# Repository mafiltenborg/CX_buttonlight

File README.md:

# What's this?
Incandescent bulbs are used in the most bizarre places in older cars - and they're often hard to replace when they burn out.
This repo holds an absolutely tiny pcb with LEDs, designed to replace one of these specialty bulb-PITAs - once and for all!

# Which & where
The particular bulb being replicated/upgraded is located inside the toggle-contacts for eg electric windows or demister switch in the Citroen CX S2 (late model '86 onwards). Replacing requires disassembly and fairly good motorskills on your part. The design uses 0805 SMDs, making it, well, possible as least. I'm too old for 0402...

# How
To replace, get hold of a number of the little PCBs (17 x 5,5mm) and solder them up. 
Next, for every contact you want to upgrade, do
* Open up your contact and extract the yellow opaque plastic thingamabob.
* Remove the burnt-out bulb and slide in a LED-replacement circuit. Re-wire the yellow thingamabob.
* Plonk in the thingamabob and do a test run. If it doesn't light up, try turning it 180 degrees - polarity matters...

Further tweaks may include modding the value of R2 to get a sensible light output. LEDs are in fact quite bright and 'much' may not be the right choice for you. The circuit is not designed for power hungry LEDs as it uses a linear regulator. 

LEDs differ. To figure out the value of R2, use the formula

Vout = 1.25 * (1 + R2/R1)

To calculate.

Don't modify R1, as this may create instability.

-----------------------
Nov. 2025 update: This design has sparked development of a more userfriendly successor. More light and less hassle too. If interested, have a look [here](https://github.com/mafiltenborg/CX-buttonlight_v2)...

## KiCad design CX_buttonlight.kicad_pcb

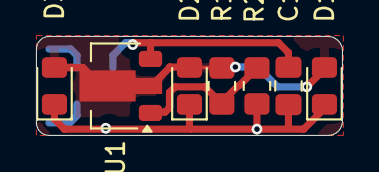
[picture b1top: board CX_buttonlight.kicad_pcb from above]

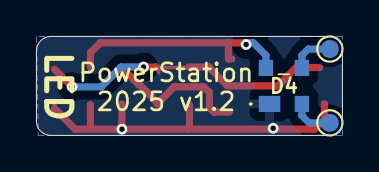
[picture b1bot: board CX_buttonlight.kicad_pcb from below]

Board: 2 copper layers, 17.0 x 5.5 mm, 10 parts (3 on the bottom side), 6 nets.

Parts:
C1: 100nF; C_0805_2012Metric_Pad1.18x1.45mm_HandSolder
D1, D2, D3: LED; LED_0805_2012Metric_Pad1.15x1.40mm_HandSolder
D4: BAS4002ARPPE6327HTSA1
Ground1: Ground; TestPoint_Pad_D1.0mm
R1: 470R; R_0805_2012Metric_Pad1.20x1.40mm_HandSolder
R2: 220R; R_0805_2012Metric_Pad1.20x1.40mm_HandSolder
Supply1: 12V; TestPoint_Pad_D1.0mm
U1: LM317L_SOT-89; SOT-89-3

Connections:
GND: C1.2, D1.1 (K), D2.1 (K), D3.1 (K), D4.1 (-), R2.1
unnamed: D1.2 (A), D2.2 (A), D3.2 (A), R1.2, U1.2 (VO)
unnamed: C1.1, D4.4 (+), U1.3 (VI)
unnamed: D4.2 (~_1), Supply1.1
unnamed: D4.3 (~_2), Ground1.1
unnamed: R1.1, R2.2, U1.1 (ADJ)

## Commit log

2025-10-21 v1.0
2025-10-21 v1.1 - med beskyttelsesdiode
2025-10-21 Modify README with more info.
2025-10-21 Add lockfiles to .gitignore
2025-10-24 updated design (tweaks + specs), sent to JLCPCB
2025-11-12 Update README.md
    Add link to v2
2025-11-18 Tweaks og tekster
